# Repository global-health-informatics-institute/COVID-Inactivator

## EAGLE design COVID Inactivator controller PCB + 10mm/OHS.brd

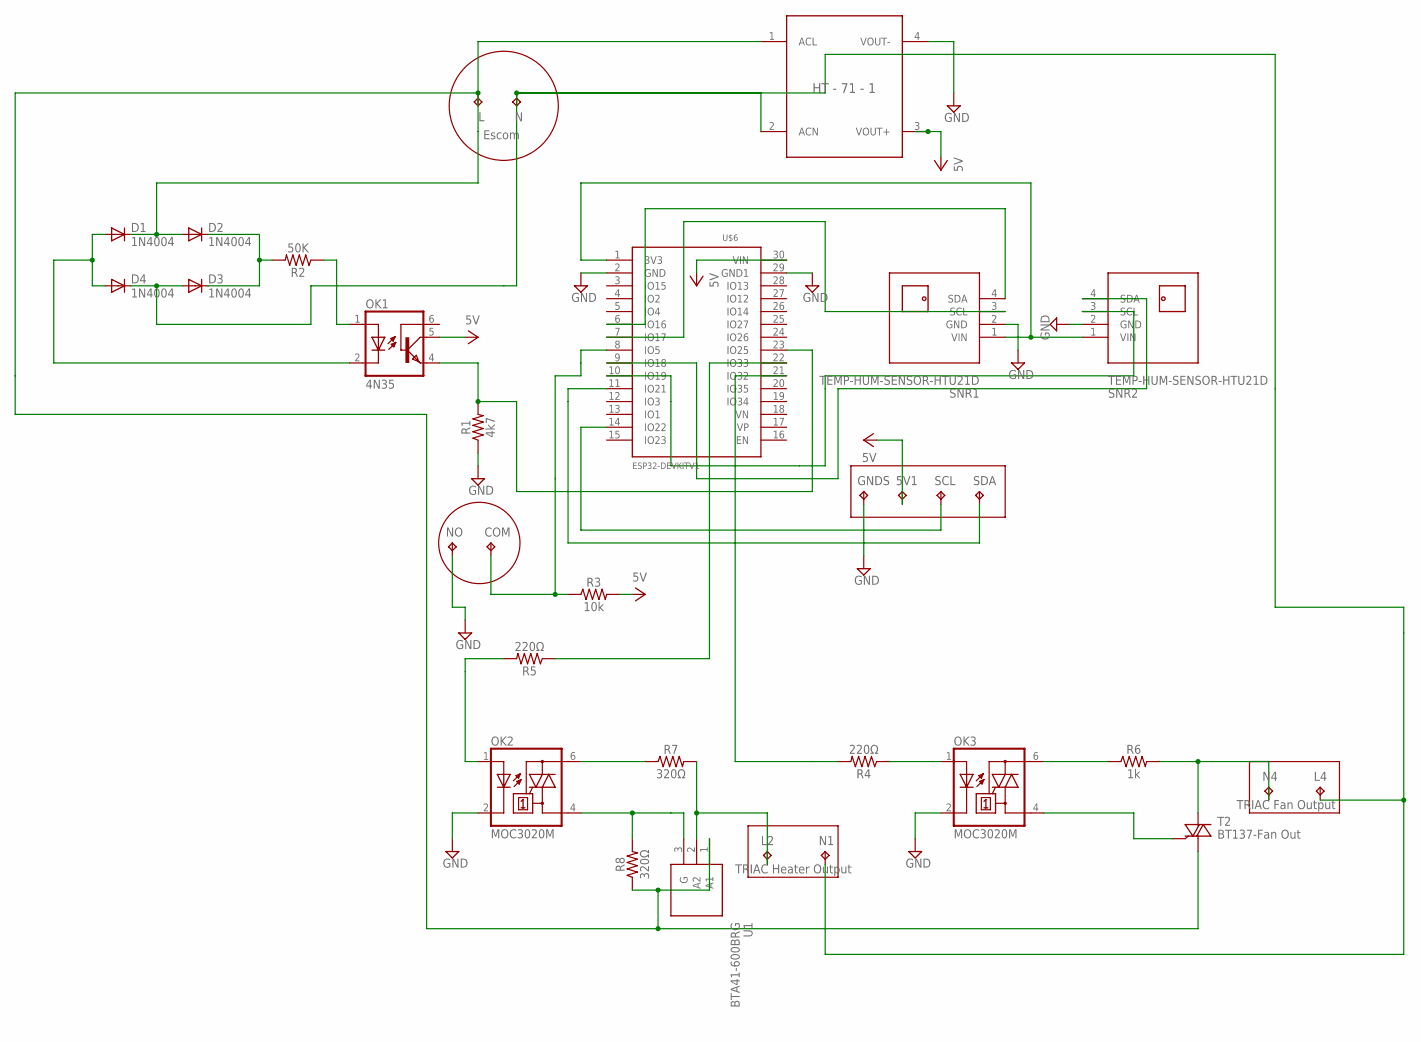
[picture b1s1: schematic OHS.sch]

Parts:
5V1: TPPAD1-20Y; P1-20Y
COM: TPPAD1-20Y; P1-20Y
D1, D2, D3, D4: 1N4004; DO41-10
GNDS: TPPAD1-20Y; P1-20Y
L, L2, L4: TPPAD1-20Y; P1-20Y
N, N1, N4: TPPAD1-20Y; P1-20Y
NO: TPPAD1-20Y; P1-20Y
OK1: 4N35; DIL06
OK2, OK3: MOC3020M; DIL06
R1: 4k7; AXIAL-0.3
R2: 50K; AXIAL-0.3
R3: 10k; AXIAL-0.3
R4, R5: 220Ω; AXIAL-0.3
R6: 1k; AXIAL-0.3
R7, R8: 320Ω; AXIAL-0.3
SCL: TPPAD1-20Y; P1-20Y
SDA: TPPAD1-20Y; P1-20Y
SNR1, SNR2: TEMP-HUM-SENSOR-HTU21D
T2: BT137-Fan Out; TO220BV
U1: BTA41-600BRG; TO552P460X1530X2985-3P
U$1: AD-DC-240-5; HT-71-1
U$6: ESP32DEVKITV1; ESP32-DEVKITV1

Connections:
GND: GNDS.TP, NO.TP, OK2.2 (C), OK3.2 (C), R1.P$1 (1), SNR1.2 (GND), SNR2.2 (GND), U$1.4 (VOUT-), U$6.2 (GND), U$6.29 (GND1)
unnamed: OK3.6 (A2), R6.P$1 (1)
unnamed: SNR2.3 (SCL), U$6.10 (IO19)
unnamed: SNR2.4 (SDA), U$6.9 (IO18)
unnamed: SNR1.3 (SCL), U$6.7 (IO17)
unnamed: OK2.6 (A2), R7.P$1 (1)
unnamed: D3.A, D4.C, L4.TP, N.TP, N1.TP, U$1.2 (ACN)
unnamed: D1.C, D2.A, L.TP, R8.P$1 (1), T2.T1 (A1), U1.1 (A1), U$1.1 (ACL)
unnamed: D2.C, D3.C, R2.P$2 (2)
unnamed: SNR1.4 (SDA), U$6.6 (IO16)
unnamed: N4.TP, R6.P$2 (2), T2.T2 (A2)
unnamed: D1.A, D4.A, OK1.2 (C)
unnamed: SNR1.1 (VIN), SNR2.1 (VIN), U$6.1 (3V3)
unnamed: OK1.1 (A), R2.P$1 (1)
unnamed: OK3.4 (A1), T2.G
unnamed: OK2.4 (A1), R8.P$2 (2), U1.3 (G)
unnamed: OK1.4 (EMI), R1.P$2 (2), U$6.23 (IO25)
unnamed: COM.TP, R3.P$1 (1), U$6.8 (IO5)
unnamed: L2.TP, R7.P$2 (2), U1.2 (A2)
unnamed: SDA.TP, U$6.11 (IO21)
unnamed: R5.P$1 (1), U$6.22 (IO33)
unnamed: R4.P$2 (2), U$6.21 (IO32)
unnamed: SCL.TP, U$6.14 (IO22)
unnamed: OK2.1 (A), R5.P$2 (2)
unnamed: OK3.1 (A), R4.P$1 (1)
VCC: 5V1.TP, OK1.5 (COL), R3.P$2 (2), U$1.3 (VOUT+), U$6.30 (VIN)

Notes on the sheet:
Escom
TRIAC Heater Output
TRIAC Fan Output

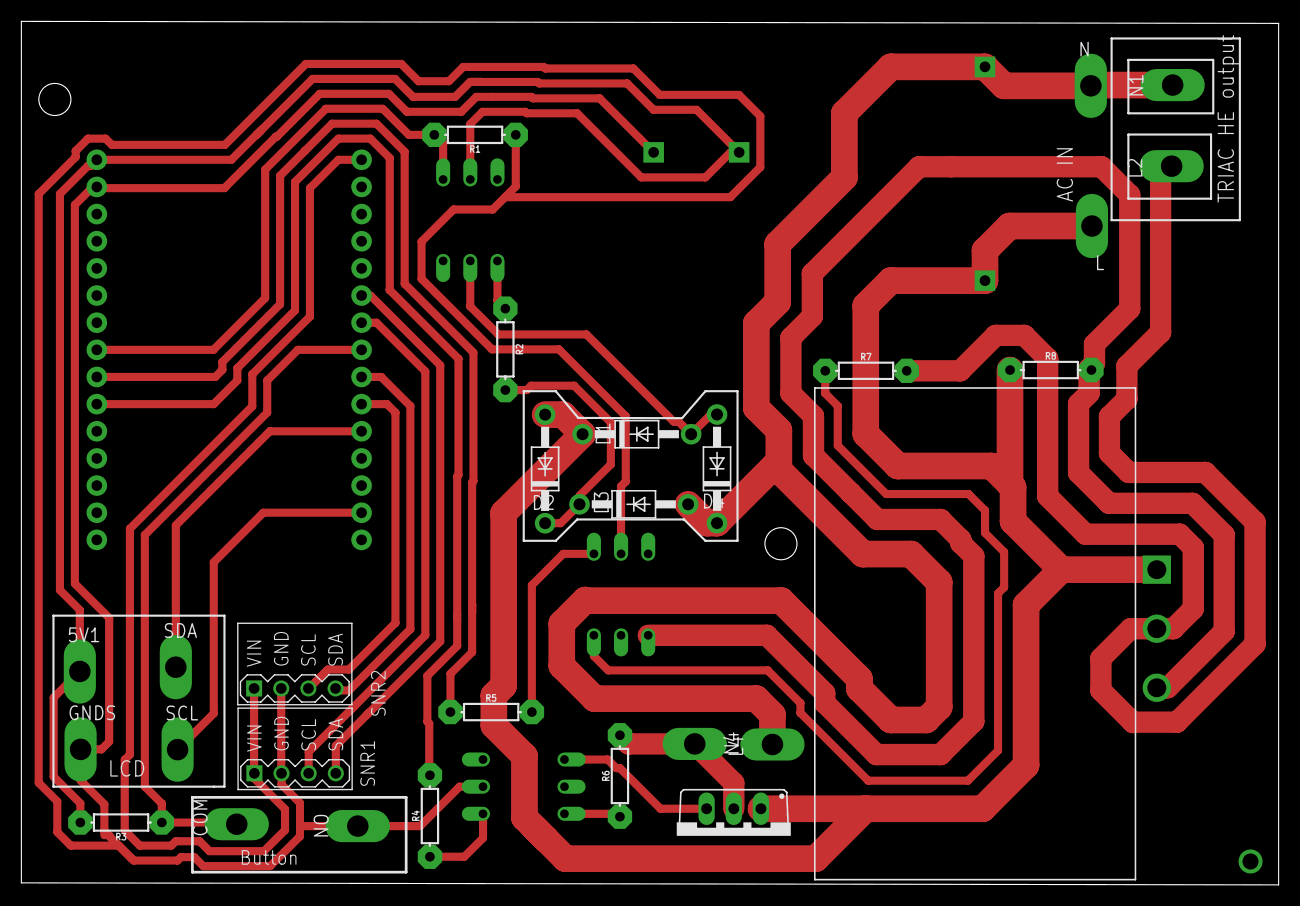
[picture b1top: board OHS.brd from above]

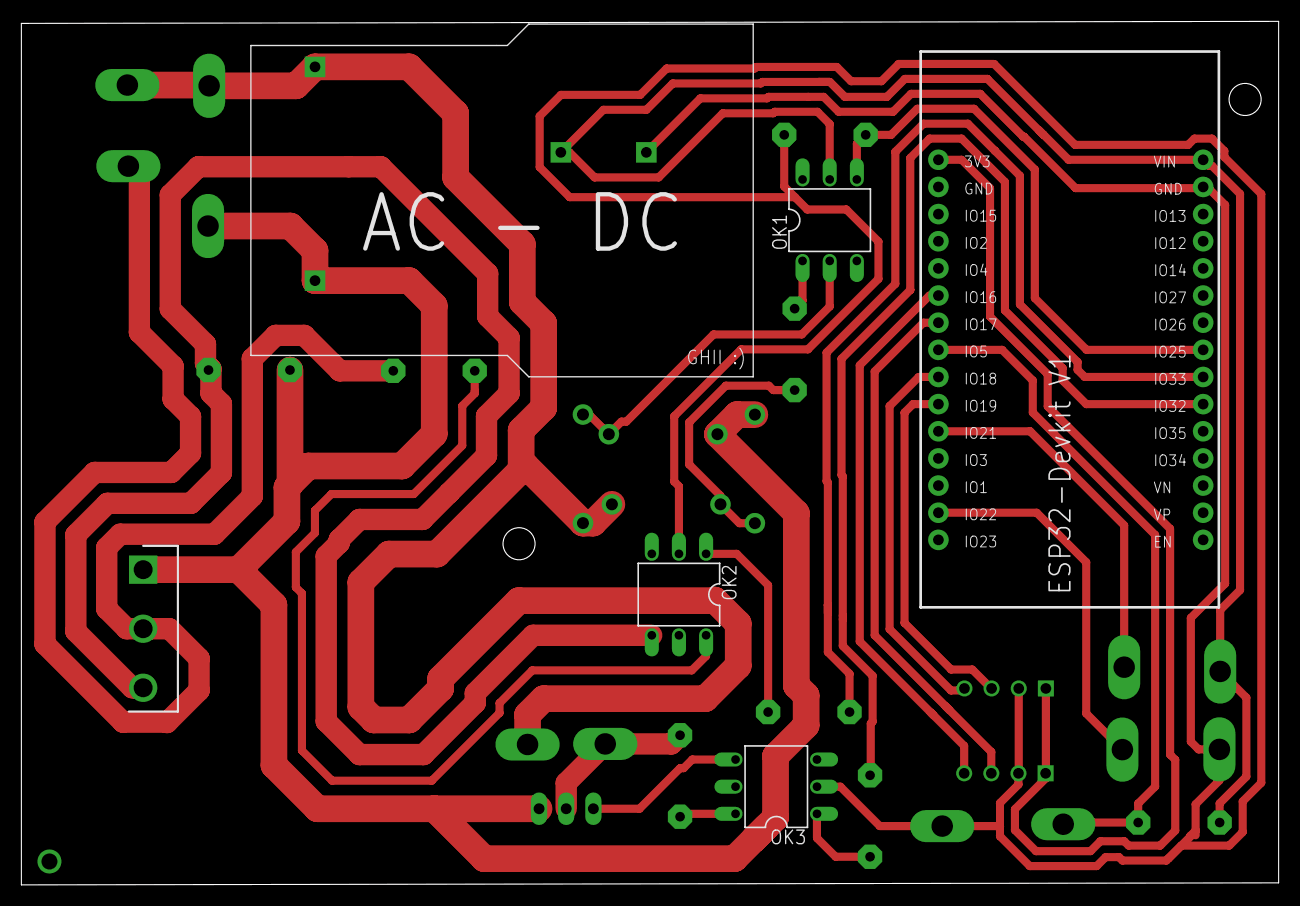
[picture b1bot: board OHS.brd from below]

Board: 2 copper layers, 117.6 x 80.8 mm, 33 parts (6 on the bottom side), 26 nets.

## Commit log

2020-04-14 Arduino file
2020-04-27 Rename Oven_Sterilizer.ino to COVID_inactivator.ino
2020-04-27 Rename Oven_Sterilizer_V2.ino to COVID_inactivator_V2.ino
2020-04-27 Rename Oven_Sterilizer/COVID_inactivator.ino to COVID_inactivator/COVID_inactivator.ino
2020-04-27 Rename Oven_Sterilizer/COVID_inactivator_V2.ino to COVID_inactivator/COVID_inactivator_V2.ino
2020-05-07 PCB design for Covid Inactivater control
2020-05-28 This is the current version of PCB being used with Updated Schematic

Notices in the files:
parts and their libraries:
SparkFun-Resistors: Licensing: Creative Commons ShareAlike 4.0 International - https://creativecommons.org/licenses/by-sa/4.0
GHIdiy-modules: Released under the Creative Commons Attribution 4.0 International License: http://creativecommons.org/licenses/by/4.0
